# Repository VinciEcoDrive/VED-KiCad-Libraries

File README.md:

# 🚀 VED KiCad Libraries

Welcome — this repo contains the curated KiCad 9-compatible libraries used by the VinciEcoDrive team. It's packaged for easy installation via KiCad's Plugin & Content Manager (PCM).

Quick overview

- 📦 Symbols: `.kicad_sym`
- 🖼️ Footprints: `.kicad_mod` inside `.pretty` folders
- 🧩 3D models: `.step` / `.wrl`

## ⚡️ Quick install (KiCad PCM)

1. Open KiCad → Preferences → Manage Plugin and Content Manager Repositories.
2. Click Add and paste this URL:
```
   https://vinciecodrive.github.io/VED-KiCad-Libraries/repository.json
```

3. Ensure the repository is enabled, open Plugin & Content Manager, find “VinciEcoDrive Libraries” and click Install.
4. After a release, click Refresh in PCM to see updates.

Note: GitHub Pages may take ~2–10 minutes to publish a new release.

## 💻 Install (advanced) — manual library tables

If you prefer to use the repo directly without PCM, follow these manual steps to add the libraries to KiCad.

1. Clone the repo somewhere consistent (example paths):

   - Windows: `C:\EE\kicad\VinciEcoDrive`
   - Linux/macOS: `~/EE/kicad/VinciEcoDrive`

2. Define an environment variable in KiCad (Preferences → Configure Paths):

   - Name: `KICAD_VED_LIB`
   - Value: path to the archive root (the folder containing `symbols/`, `footprints/`, `3dmodels/`)

3. Add symbol libraries (global):

   - Preferences → Manage Symbol Libraries → Global → Add
   - Nickname examples: `VED_Connectors`, `VED_Integrated_Circuits`, etc.
   - Library path example: `${KICAD_VED_LIB}/symbols/VED_Connectors.kicad_sym`

4. Add footprint libraries (global):

   - Preferences → Manage Footprint Libraries → Global → Add
   - Path example: `${KICAD_VED_LIB}/footprints/VED_Connectors.pretty`

5. 3D models

   - 3D models are referenced by footprints using relative paths or `${KICAD_VED_LIB}`.
   - Ensure your `KICAD_VED_LIB` points to the folder that contains the `3dmodels/` folder so footprints can find the models.

Notes

- Using an environment path keeps library entries portable across machines. If multiple team members use the same convention, everyone can reuse the same global table entries.
- When editing tables, prefer Global if the libraries are used across several projects; use Project tables for project-local overrides.

## 📦 Release a new version

Follow these steps to publish a release that users can install via PCM:

1. Prepare `main`
   - Merge all PRs targeted for the release.
   - Update `CHANGELOG.md` with highlights.

2. Create a tag (use [semver](https://semver.org/)):

   - Example: `git tag -a v1.3.0 -m "VinciEcoDrive libs 1.3.0"`
   - Push: `git push origin v1.3.0`

3. CI will (automated):
   - Zip `package/` into `vinciecodrive-libs-<version>.zip`
   - Generate `packages.json` and `repository.json`
   - Publish artifacts to the `gh-pages` branch

4. Verify deployment URLs
   - repository.json: https://vinciecodrive.github.io/VED-KiCad-Libraries/repository.json
   - packages.json:   https://vinciecodrive.github.io/VED-KiCad-Libraries/packages.json

5. Tell users to Refresh in KiCad PCM and update the package.

## 🧪 Tips & troubleshooting

- If PCM doesn't show the new release immediately, wait a few minutes then click Refresh.
- If an install fails, check the GitHub Actions logs (CI) and confirm `repository.json` is accessible.

## 🤝 Contact

- For library content updates: coordinate with the team working on the specific symbol/footprint.
- CI / repo maintainer: Théo HARDY — [theo.hardy@edu.devinci.fr](mailto:theo.hardy@edu.devinci.fr)

---

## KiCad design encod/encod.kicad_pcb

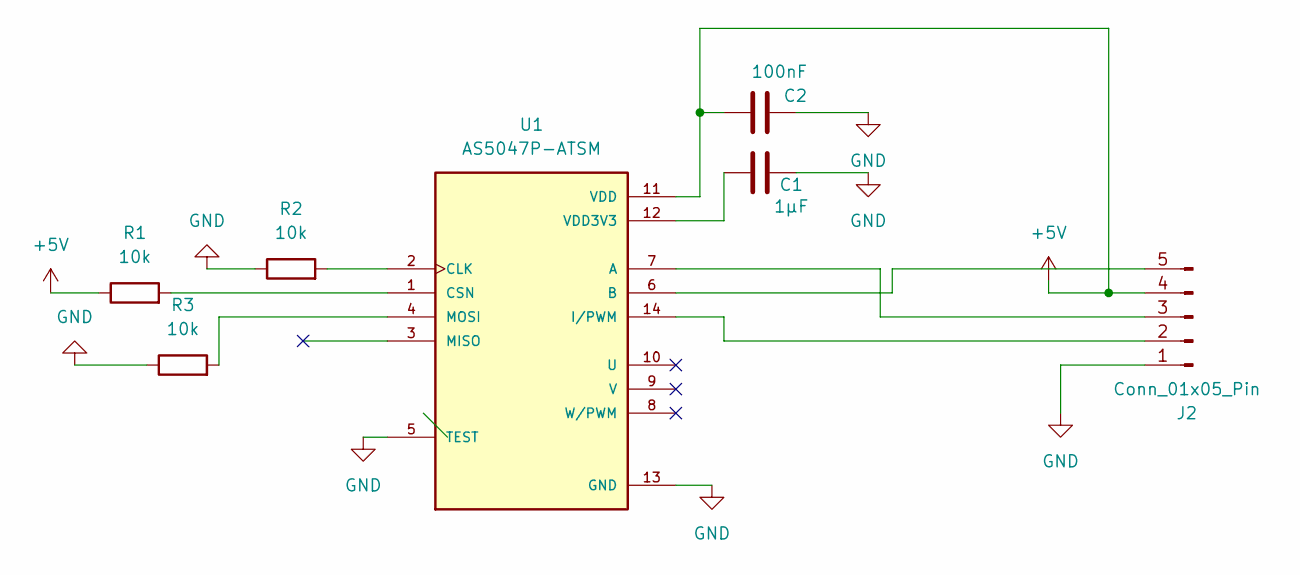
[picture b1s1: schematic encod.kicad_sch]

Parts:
C1: 1µF; C_0805_2012Metric
C2: 100nF; C_0805_2012Metric
J2: Conn_01x05_Pin; WR-WTB-1x05-2.54mm-Horizontal-61900511021
R1, R2, R3: 10k; R_0805_2012Metric
U1: AS5047P-ATSM; Part Number AS5047P-ATSM

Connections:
+5V: C2.2, J2.4, R1.1, U1.11 (VDD)
GND: C1.2, C2.1, J2.1, R2.1, R3.1, U1.5 (TEST), U1.13 (GND)
unnamed: J2.2, U1.14 (I/PWM)
unnamed: J2.3, U1.7 (A)
unnamed: J2.5, U1.6 (B)
unnamed: R2.2, U1.2 (CLK)
unnamed: R1.2, U1.1 (CSN)
unnamed: R3.2, U1.4 (MOSI)
unnamed: C1.1, U1.12 (VDD3V3)

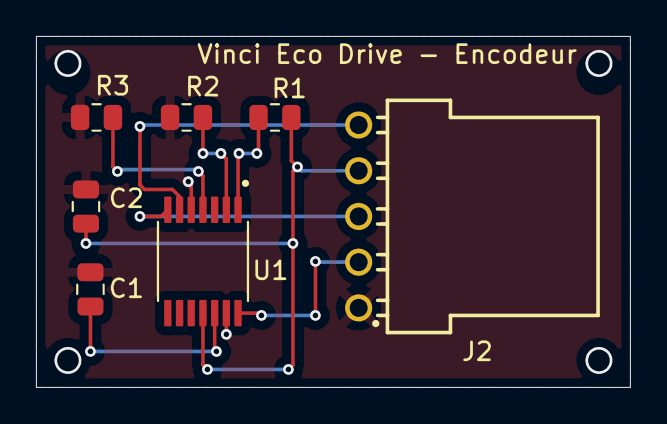
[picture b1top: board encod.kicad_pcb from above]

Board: 2 copper layers, 33.0 x 19.5 mm, 7 parts (0 on the bottom side), 9 nets.

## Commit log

2025-10-29 Add PCM workflow icon and readme
2025-10-29 Change release site name
2025-10-29 fix root rame
2025-10-29 change repo arborescence to ease ci
2025-10-29 Change pcm.yml
2025-10-29 deploy: 7019bb064d1199734342ba536a251c077182e9ee
2025-10-29 Fix PCM
2025-10-29 deploy: 831eb576de67aadd344454142e8c28917644dc0c
2025-10-29 deploy: 9899dce9f08d393ae1eb14caf0a108bcf05d0fb7
2025-10-29 Fix pcm file not KiCad compatible
2025-10-29 deploy: aa4fcdfeb7cae4c28df3f1f10e7d89e1e1176696
2025-10-29 Fix pcm.yml
2025-10-29 deploy: 4123910d076cc5e4a2ec201cc538b9d386f55d39
2025-10-29 Fix Workflow
2025-10-29 deploy: 0f4722a8ffc4d3ae01383f7859d747fc0f4e37d8
2025-10-29 Add icon
2025-10-29 deploy: 5b5cfd4b4cef31d1b2d745c822c557553883948a
2025-10-29 Update to add Icon
2025-10-29 deploy: a0dcbdbdd6df5c6f37149ae88a2fbab92cabf5a3
2025-10-29 Add logo image to README
2025-10-29 deploy: bc86f088f0d74ac8fc25d48b19f16cfdd7135abe
2025-10-29 Fix image path for VED logo in README
2025-10-30 Add README and icon copying to dist in CI workflow
2025-10-30 deploy: c7f9c0b2458793b3bfa37364c9700e7725279fbb
2025-10-30 Fix icon path in workflow to ensure correct copying to dist
2025-10-30 deploy: 10bda4e029b2b146b17ed8188306091dc5c96e7e
2025-10-30 Fix README and icon copying in CI workflow
2025-10-30 deploy: 7d8bc14309b0e6e1adeff6f157639a56ef93941c
2025-10-30 Fix icon copying path in CI workflow to ensure correct placement in dist
2025-10-30 Fix numbering and formatting in installation instructions in README
2025-10-30 Refactor icon copying logic in CI workflow for improved readability and maintainability
2025-10-30 deploy: ab5cc0ca93cace4ab96066b11bdbfe69ea036e12
2025-10-30 Improve icon copying logic in CI workflow to use 'install -D' for atomic directory creation
2025-10-30 deploy: 1015486f5f8cce86c75b0ca7f9185fc85ef40d7f
2025-10-30 Update formating
2025-10-30 add first component: esp32
2025-10-30 deploy: aa8aeb3c48bf9d9a0bce4794012d8476892b4a0e
2025-10-30 add component: RJ45-615008141321
2025-10-30 deploy: 42e966ee522585f3aa67a8546d70ee3304b2052a
2025-10-30 Added License
2025-10-30 fix orthograph
2025-11-06 add gitignore ; remove .bak files
2025-11-06 update 3d models
2025-11-06 deploy: 437fa4816e29164cd0e2b64fb64b1ee602d119f3
2025-11-06 add library : VED_Passive_Components
2025-11-06 deploy: cf9fe30bb8b00b1b220cfffff8912f8ed9c8f185
2025-11-06 fix: 3d models
2025-11-06 deploy: f510241cac054cf5129778c38ff5cae0dc3e6d2c
2025-11-06 Add : connector WR-WTB and Diode
2025-11-06 deploy: 6bac78bf65fa2b69a1fd48ebc5d03f9bc38f3285
2025-11-06 add:current-sensor-acs770
2025-11-06 deploy: adce9013edf10c5848d0ee6879fdcb9d85358192
2025-11-06 add footprint : led, fexed step down regulator, relay
2025-11-06 add new components pwm and power supply
2025-11-06 deploy: 5917136d56f0a8137e7d963e8761f231e4da1558
2025-11-06 add:capacitor,diode,fuse-holder
2025-11-06 deploy: 356540794354cc65ee9a3c1b48892a5bff4c2e14
2025-11-07 add:data-connection,mosfet,temp-sensor
2025-11-07 add footprint : second connector wr-wtb
2025-11-07 add : symbol fixed step down regulator
2025-11-07 deploy: 59c7d88960a243c61e8f6e7d5d30f7c4ee9c765a
2025-11-07 deploy: eb1078eb9d8708060fe88b2fdee09029e15cd11f
2025-11-12 modif : symbole fixed step down regulator (forgot one s in footprint)
2025-11-13 deploy: 252425db7be4b152b72aac7584d4d8907b6c933f
2025-11-13 add CONTRIBUTING.md
2025-11-13 fix-RJ45-component
2025-11-13 deploy: 93c1f14431cbbd2b5bb62d4e0f2c34e23ef5b457
2025-11-13 add : ?
2025-11-14 add footprints and 3d models
2025-11-14 deploy: 0c5c15c849075fad20dcfe048415a4eedd3ca073
2025-11-14 fix-3d-models
2025-11-14 deploy: 099bc3467b9ec9c36f6c072bf6c09d5886e762e7
2025-11-14 deploy: ca3dfe173c400f748b2120c44ff3701324e7d529
2025-11-14 correction of symbols and footprints : mosfet and current sensor
2025-11-14 Update contributing guidelines and installation instructions in documentation
2025-11-14 deploy: c843f87edd79118717d3705625d6c7bc8bb3e00f
2025-11-15 modif link footprint in symbol mosfet
2025-11-15 deploy: 7d49dbf95de49745ba86a0731c07f1e7249394b2
2025-11-19 Enhance README layout by adding logo and improving title formatting
2025-11-19 Fix table styling in README for improved layout and consistency
2025-11-19 Refactor README header to simplify structure by removing table
2025-11-20 Add commit verification step to ensure changes before tagging a new release
2025-11-20 deploy: 2c1e08921a054c4a3066aae840fbf56d7da4c8a7
2025-11-20 modif temp sensor : symbole + footprint
2025-11-20 modif link temp sensor footprit and add 2 relays symboles and footprints
2025-11-21 deploy: 43504b6df40c50a0a28749db23578a2196d11337
2025-11-21 modif footprint current sensor acs770
2025-11-21 deploy: 71310277b70d7c6b1a8ee5f29d0d2d7c9a9eac14
2025-11-21 add 3d models of xt60, 2 relays, diode, led, current and temp sensor, mosfet, fuse
2025-11-21 deploy: 744ea8cc9a26049cbd79265c2f8785a6e28f1f6f
2025-11-21 deploy: e232ac8e46803fe81a6d21464319e62a4847a09d
2025-11-21 modif 3d model diode link
2025-11-21 deploy: 8c6d3ed005cb6c2fd00753064e22e9360d7b20d3
2025-11-22 add descriptions and datasheets link to symbols and modif name of current sensor footprint
2025-11-22 deploy: c075431b2ef31dc0deea158785096e065c05bb36
2025-12-03 fix esp32 3dmodel
2025-12-03 add WPME-FDSM-173010X78 symbol and update footprint
2025-12-03 deploy: 4d3899d2a5f8d619c2d75ffbbd7713c7a465f369
2025-12-03 create logos library
2025-12-03 add logos: VED, Wurth, RS, Altium
2025-12-03 deploy: 9f978059372ff337c7f4c679e7d96c6067d3055e
2025-12-04 update logos
2025-12-04 deploy: bc06db98ed3d55dc14cb2f1a7e84fb3cb7037472
2025-12-04 update altium logos
2025-12-04 deploy: 1f65d8468bfac2c49ef77b99704395d7d5c45555
2026-01-20 add component: Wurth Shielded Power Inductor 1260
2026-01-20 deploy: 9c4ada23935f75dcf145bd70115a23e366c2fb20
2026-05-29 Add AS5047P-ATSM symbol, footprint and 3d model
2026-05-29 deploy: e28bbdf802e3855212cf582800e38ab874cfabe7
2026-06-04 Nouvelle carte encodeur
